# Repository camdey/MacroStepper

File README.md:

# MacroStepper v3.0
Author: Cam Dey

Created: 2018-12-18

v2.0: 2020-01-01

v3.0: 2023-10-11 // refactor, introduces breaking changes

The MacroStepper is a fully automated macrophotography rig designed to enable a camera to take photos at precisely incremented steps. The macroStack can work with or without an automated shutter and also in manual mode if the user prefers to control the stepping themselves.

# Schematic

# Interface
**Home Screen**
 - House icon: _run homing sequence for the rail, finds min and max positions of the rail_
 - X icon: _clears the settings from the auto mode_
 
**Manual Screen**
 - Step Dist: _press to set distance per movement of the motor_
	 - _value is the distance per movement covered by the rail in millimetres_
 - Step Nr: _number of movements taken in manual mode_
 - Rail Pos: _current position of the camera on the rail_
 - Aperture icon: _press to enable/disable automated shutter_
 - X icon: _press to clear step count_
 - Arrows: _for increment/decrementing the Step Size if enabled or moving the rail forward/back otherwise_

**Auto Screen**
 - Step Dist: _press to set distance per movement of the motor_
	 - _value is the distance per movement covered by the rail in millimetres_
 - Est. Time: _estimated time remaining in autoStack procedure. Takes into account shutter delay and the recycle time of the flash unit_
 - Progress: _number of movements completed out of total number of movements in procedure_
 - Aperture icon: _press to enable/disable automated shutter_
 - Cog icon: _opens the config menu for the auto mode_
 - Play symbol: _used to increment Step Size if enabled, otherwise used for starting the autoStack procedure_
 - Pause symbol: _used to decrement Step Size if enabled, otherwise used for pausing the autoStack procedure_

**Config Screen**

 - START: _press to set the start position for the autoStack procedure. Will automatically change to current position when enabled, use joystick or arrows to move rail into correct position_
 - END: _press to set the end position for the autoStack procedure. Will automatically change to current position when enabled, use joystick or arrows to move rail into correct position_
 - RUN: _will move the camera rail to the START position, slowly increment through the autoStack range until it reaches the END, and then move back to the START position_
 - Clock symbol: _press to change the shutter delay between taking photos after each movement of the stepper motor_
 - Arrows: _used to increment/decrement shutter delay or move the position of the rail_

# Functionality
**Flash/Shutter Control**
The camera shutter is controlled by the Arduino via cable where a HIGH signal is sent to a transistor to short the Shutter and Focus pins of the Sony A6000 to ground. The duration of this signal is determined by an output signal from a PC sync cable. This cable is connected to the output of a Godox X1T-S transmitter. This transmitter sends a LOW signal for several milliseconds when the flash is ready to trigger. When the low signal is received by the Arduino, the shutter line goes LOW and the Shutter and Focus pins are returned to nominal state.

**Distance settings**
The step distance setting refers to the distance travelled by the rail per movement. A movement is the sequence of steps required by the stepper motor to travel the set distance. The default distance per step in my case was 25μm, calculated by the following: screw pitch / steps per revolution / gear reduction. My rail had a 1mm pitch and 1:2 gear reduction, while the motor takes 200 steps per revolution.

If the step size is set to 100μm, this equates to four steps at 25μm each. The sequence of these four steps is termed a movement in this project.

**AutoStack Procedure**
The autoStack procedure will increment a range by a given number of movements, determined by the step distance and the start and end positions determined by the user. With a 100μm step distance and 180 steps required to go from the start position to the end position, 45 (180/4) movements are required and thus 45 photos will be taken. The procedure can be paused or reset at any stage and after completion the procedure can be restarted. Both step distance and the end position can be changed during the procedure once paused.

# Macrophotography

## What is focus stacking?

Focus stacking is a method popular within the field of macrophotography where multiple photos of the same subject are taken at different focus depths and then merged together with software. This enables a macro lens with a shallow depth of field to produce an image of a subject that is fully in focus, even if the subject is physically longer than the depth of field of the lens.

## What do you need for Macrophotography?

While you can create a focus stack just with handheld photos taken at different distances from the subject, typically a **macro rail** is used to help with this process. A macro rail allows you to move a camera attached to a platform by very specific distances along a fixed rail or slide. By turning a handle or knob of the macro rail, the camera can be incremented along the rail by distances as small as 25μm or as large as the rail is long.

**Macro Rail**
For this project, you will need a macro rail that can be attached to a stepper motor. Many commercially available macro rails can be retrofitted with a pinion gear to accept a belt, which is in turn attached to a pinion gear on a stepper motor. Other macro rails are designed to interface directly with a stepper motor, especially those designed to be used for CNC machines or 3D printing.

**Stepper Motor**
A stepper motor is required to move the macro rail automatically. You can do this manually, and many do, but after awhile you get sick of the repetitive process of "move camera rail, take photo, move camera rail, take photo".

There are many types of stepper motors available but for this project I would recommend one in the NEMA 17 form factor with either 200 (1.8°) or 400 (0.9°) steps per revolution and between 1A and 2A current rating. The current rating is important for the load the stepper motor can move and hold but it is not the only determiner of this. A motor with a holding torque of at least 3kg-cm should be adequate.

The voltage of the motor is less important as you can supply more voltage than the rated voltage of the motor. More supply voltage typically equals a faster motor.

**Camera and Lens**
Any DSLR or mirrorless camera will be suitable. A macro lens of your choosing is also sufficient.

**Lighting**
I would recommend buying a flash for your camera, preferably wireless. Macrophotography often deals with very low amounts of light and high apertures so a flash is particularly useful. This project is designed to work with the shutter of a Sony multi-terminal port for triggering the shutter and a PC sync cable for detecting the output signal of the flash being triggered but either of these can be changed to the communication methods required for your camera and flash.

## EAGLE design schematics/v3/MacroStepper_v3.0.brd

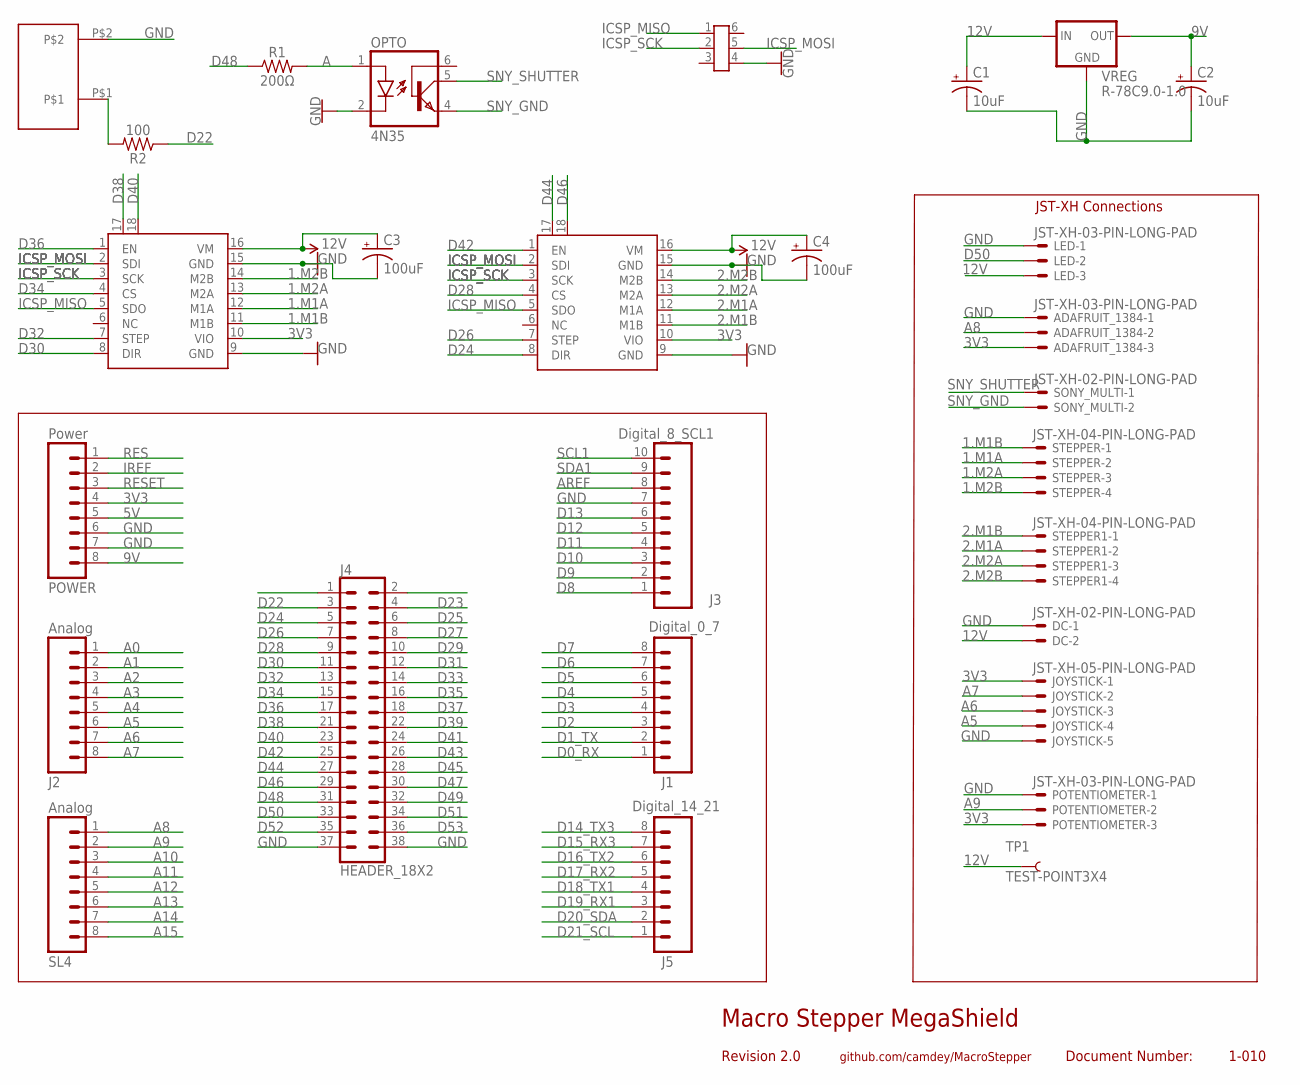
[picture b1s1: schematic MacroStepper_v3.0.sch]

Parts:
ADAFRUIT_1384: JST-XH-03-PIN-LONG-PAD; JST-XH-03-PACKAGE-LONG-PAD
C1, C2: 10uF; CPOL-RADIAL-2.5MM-5MM
C3, C4: 100uF; CPOL-RADIAL-2.5MM-6.5MM
DC: JST-XH-02-PIN-LONG-PAD; JST-XH-02-PACKAGE-LONG-PAD
ICSP: MEGA_ICSP
J1: Digital_0_7; 1X08
J2: Analog; 1X08
J3: Digital_8_SCL1; 1X10
J4: HEADER_18X2; 2X18
J5: Digital_14_21; 1X08
JOYSTICK: JST-XH-05-PIN-LONG-PAD; JST-XH-05-PACKAGE-LONG-PAD
LED: JST-XH-03-PIN-LONG-PAD; JST-XH-03-PACKAGE-LONG-PAD
OPTO: 4N35; DIL06
PIEZO: PS1240P02BT
POTENTIOMETER: JST-XH-03-PIN-LONG-PAD; JST-XH-03-PACKAGE-LONG-PAD
POWER: Power; 1X08
R1: 200Ω; AXIAL-0.3
R2: 100; AXIAL-0.3
SL4: Analog; 1X08
SONY_MULTI: JST-XH-02-PIN-LONG-PAD; JST-XH-02-PACKAGE-LONG-PAD
STEPPER, STEPPER1: JST-XH-04-PIN-LONG-PAD; JST-XH-04-PACKAGE-LONG-PAD
TMC5160_1, TMC5160_2: TMC2130; DIL16
TP1: TEST-POINT3X4; PAD.03X.04
VREG: R-78C9.0-1.0; SIP3

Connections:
1.M1A: STEPPER.2, TMC5160_1.12 (M1A)
1.M1B: STEPPER.1, TMC5160_1.11 (M1B)
1.M2A: STEPPER.3, TMC5160_1.13 (M2A)
1.M2B: STEPPER.4, TMC5160_1.14 (M2B)
2.M1A: STEPPER1.2, TMC5160_2.12 (M1A)
2.M1B: STEPPER1.1, TMC5160_2.11 (M1B)
2.M2A: STEPPER1.3, TMC5160_2.13 (M2A)
2.M2B: STEPPER1.4, TMC5160_2.14 (M2B)
3V3: ADAFRUIT_1384.3, JOYSTICK.1, POTENTIOMETER.3, POWER.4, TMC5160_1.10 (VIO), TMC5160_2.10 (VIO)
5V: POWER.5
9V: C2.1 (+), POWER.8, VREG.3 (OUT)
12V: C1.1 (+), C3.1 (+), C4.1 (+), DC.2, LED.3, TMC5160_1.16 (VM), TMC5160_2.16 (VM), TP1.P$1, VREG.1 (IN)
A: OPTO.1 (A), R1.P$2 (2)
A0: J2.1
A1: J2.2
A2: J2.3
A3: J2.4
A4: J2.5
A5: J2.6, JOYSTICK.4
A6: J2.7, JOYSTICK.3
A7: J2.8, JOYSTICK.2
A8: ADAFRUIT_1384.2, SL4.1
A9: POTENTIOMETER.2, SL4.2
A10: SL4.3
A11: SL4.4
A12: SL4.5
A13: SL4.6
A14: SL4.7
A15: SL4.8
AREF: J3.8
D0_RX: J1.1
D1_TX: J1.2
D2: J1.3
D3: J1.4
D4: J1.5
D5: J1.6
D6: J1.7
D7: J1.8
D8: J3.1
D9: J3.2
D10: J3.3
D11: J3.4
D12: J3.5
D13: J3.6
D14_TX3: J5.8
D15_RX3: J5.7
D16_TX2: J5.6
D17_RX2: J5.5
D18_TX1: J5.4
D19_RX1: J5.3
D20_SDA: J5.2
D21_SCL: J5.1
D22: J4.3 (D22), R2.P$1 (1)
D23: J4.4 (D23)
D24: J4.5 (D24), TMC5160_2.8 (DIR)
D25: J4.6 (D25)
D26: J4.7 (D26), TMC5160_2.7 (STEP)
D27: J4.8 (D27)
D28: J4.9 (D28), TMC5160_2.4 (CS)
D29: J4.10 (D29)
D30: J4.11 (D30), TMC5160_1.8 (DIR)
D31: J4.12 (D31)
D32: J4.13 (D32), TMC5160_1.7 (STEP)
D33: J4.14 (D33)
D34: J4.15 (D34), TMC5160_1.4 (CS)
D35: J4.16 (D35)
D36: J4.17 (D36), TMC5160_1.1 (EN)
D37: J4.18 (D37)
D38: J4.21 (D38), TMC5160_1.17 (DIAG0)
D39: J4.22 (D39)
D40: J4.23 (D40), TMC5160_1.18 (DIAG1)
D41: J4.24 (D41)
D42: J4.25 (D42), TMC5160_2.1 (EN)
D43: J4.26 (D43)
D44: J4.27 (D44), TMC5160_2.17 (DIAG0)
D45: J4.28 (D45)
D46: J4.29 (D46), TMC5160_2.18 (DIAG1)
D47: J4.30 (D47)
D48: J4.31 (D48), R1.P$1 (1)
D49: J4.32 (D49)
D50: J4.33 (D50), LED.2
D51: J4.34 (D51)
D52: J4.35 (D52)
D53: J4.36 (D53)
GND: ADAFRUIT_1384.1, C1.2 (-), C2.2 (-), C3.2 (-), C4.2 (-), DC.1, ICSP.4 (GND), J3.7, J4.37 (GND), J4.38 (GND), JOYSTICK.5, LED.1, OPTO.2 (C), PIEZO.P$2, POTENTIOMETER.1, POWER.6, POWER.7, TMC5160_1.9 (GND), TMC5160_1.15 (GND), TMC5160_2.9 (GND), TMC5160_2.15 (GND), VREG.2 (GND)
ICSP_MISO: ICSP.1 (MISO), TMC5160_1.5 (SDO), TMC5160_2.5 (SDO)
ICSP_MOSI: ICSP.5 (MOSI), TMC5160_1.2 (SDI), TMC5160_2.2 (SDI)
ICSP_SCK: ICSP.2 (SCK), TMC5160_1.3 (SCK), TMC5160_2.3 (SCK)
IREF: POWER.2
unnamed: PIEZO.P$1, R2.P$2 (2)
RES: POWER.1
RESET: POWER.3
SCL1: J3.10
SDA1: J3.9
SNY_GND: OPTO.4 (EMI), SONY_MULTI.2
SNY_SHUTTER: OPTO.5 (COL), SONY_MULTI.1

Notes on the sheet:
JST-XH Connections
Macro Stepper MegaShield
Revision 2.0
github.com/camdey/MacroStepper
Document Number:
1-010

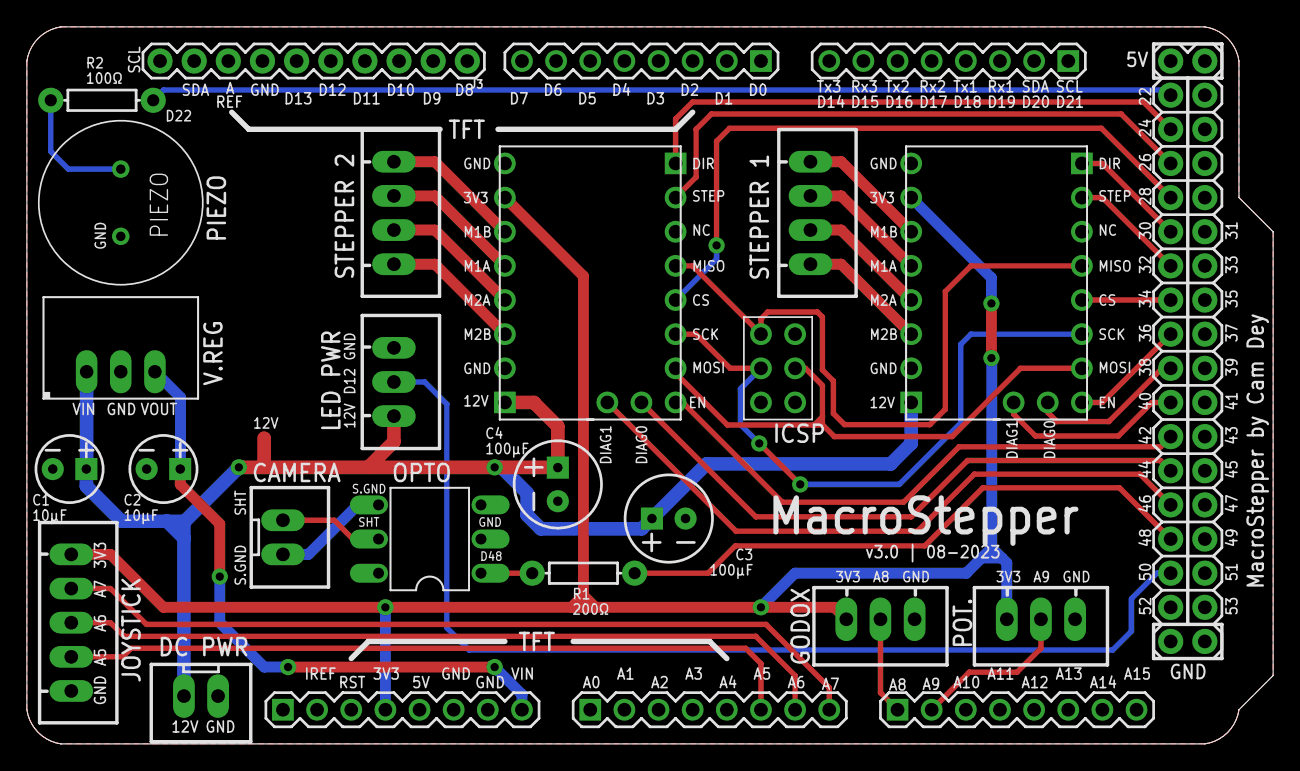
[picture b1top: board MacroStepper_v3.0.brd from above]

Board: 2 copper layers, 92.7 x 53.3 mm, 29 parts (1 on the bottom side), 39 nets.

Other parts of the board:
U$1: ARTEMIS_LOGO_LARGE

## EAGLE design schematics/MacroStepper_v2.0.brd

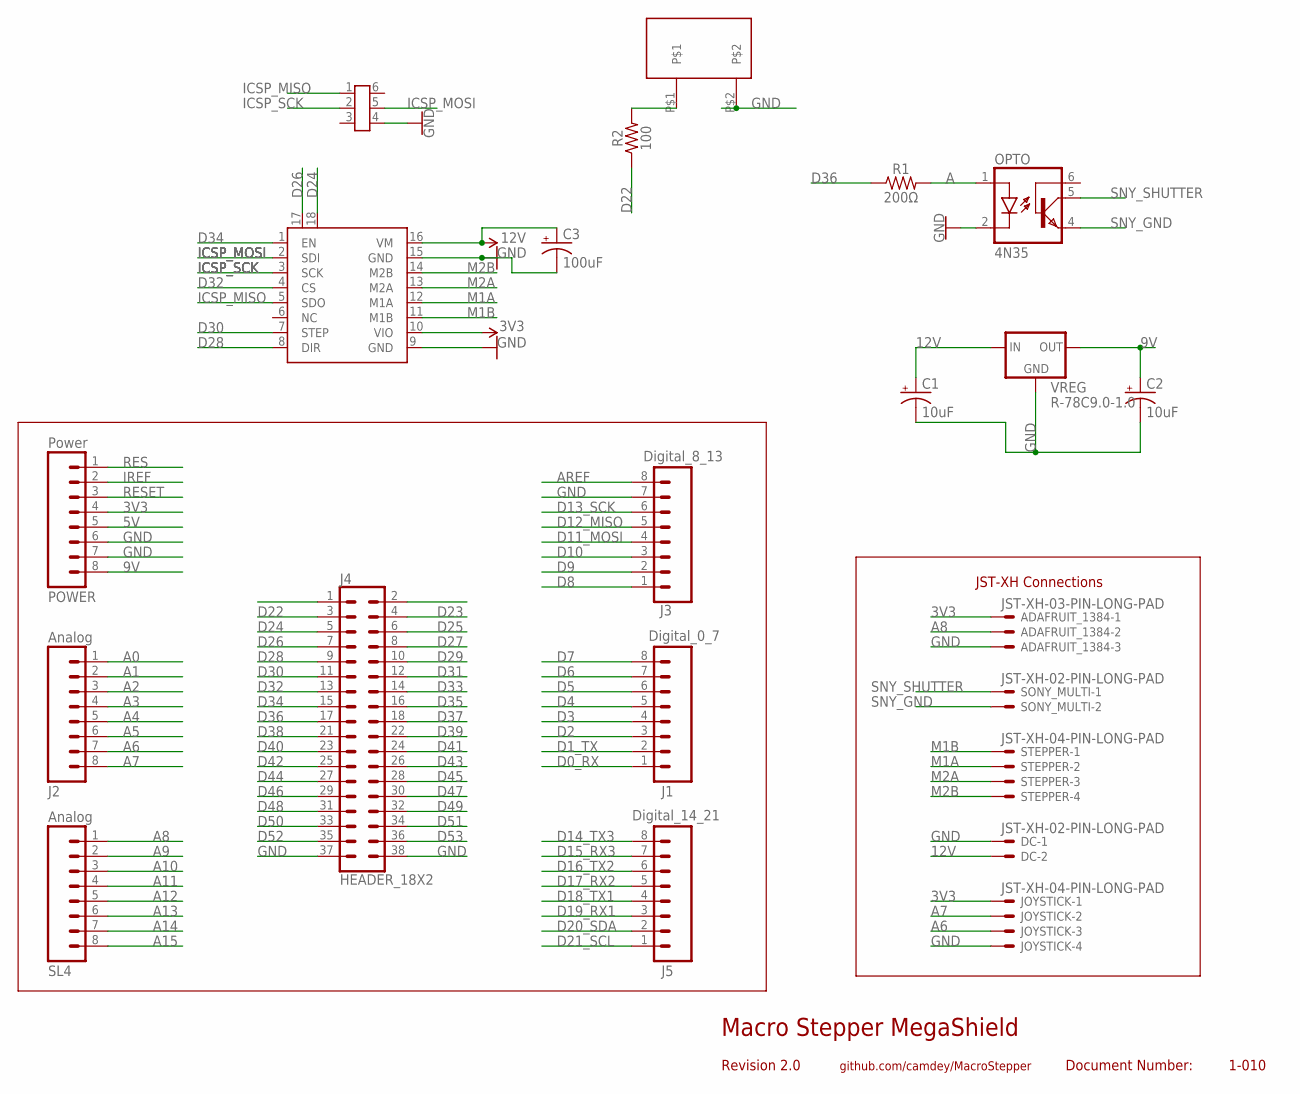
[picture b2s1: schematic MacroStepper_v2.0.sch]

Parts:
ADAFRUIT_1384: JST-XH-03-PIN-LONG-PAD; JST-XH-03-PACKAGE-LONG-PAD
C1, C2: 10uF; CPOL-RADIAL-2.5MM-5MM
C3: 100uF; CPOL-RADIAL-2.5MM-6.5MM
DC: JST-XH-02-PIN-LONG-PAD; JST-XH-02-PACKAGE-LONG-PAD
ICSP: MEGA_ICSP
J1: Digital_0_7; 1X08
J2: Analog; 1X08
J3: Digital_8_13; 1X08
J4: HEADER_18X2; 2X18
J5: Digital_14_21; 1X08
JOYSTICK: JST-XH-04-PIN-LONG-PAD; JST-XH-04-PACKAGE-LONG-PAD
OPTO: 4N35; DIL06
PIEZO: PS1240P02BT
POWER: Power; 1X08
R1: 200Ω; AXIAL-0.3
R2: 100; AXIAL-0.3
SL4: Analog; 1X08
SONY_MULTI: JST-XH-02-PIN-LONG-PAD; JST-XH-02-PACKAGE-LONG-PAD
STEPPER: JST-XH-04-PIN-LONG-PAD; JST-XH-04-PACKAGE-LONG-PAD
TMC2130: TMC2130; DIL16
VREG: R-78C9.0-1.0; SIP3

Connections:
3V3: ADAFRUIT_1384.1, JOYSTICK.1, POWER.4, TMC2130.10 (VIO)
5V: POWER.5
9V: C2.1 (+), POWER.8, VREG.3 (OUT)
12V: C1.1 (+), C3.1 (+), DC.2, TMC2130.16 (VM), VREG.1 (IN)
A: OPTO.1 (A), R1.P$2 (2)
A0: J2.1
A1: J2.2
A2: J2.3
A3: J2.4
A4: J2.5
A5: J2.6
A6: J2.7, JOYSTICK.3
A7: J2.8, JOYSTICK.2
A8: ADAFRUIT_1384.2, SL4.1
A9: SL4.2
A10: SL4.3
A11: SL4.4
A12: SL4.5
A13: SL4.6
A14: SL4.7
A15: SL4.8
AREF: J3.8
D0_RX: J1.1
D1_TX: J1.2
D2: J1.3
D3: J1.4
D4: J1.5
D5: J1.6
D6: J1.7
D7: J1.8
D8: J3.1
D9: J3.2
D10: J3.3
D11_MOSI: J3.4
D12_MISO: J3.5
D13_SCK: J3.6
D14_TX3: J5.8
D15_RX3: J5.7
D16_TX2: J5.6
D17_RX2: J5.5
D18_TX1: J5.4
D19_RX1: J5.3
D20_SDA: J5.2
D21_SCL: J5.1
D22: J4.3 (D22), R2.P$1 (1)
D23: J4.4 (D23)
D24: J4.5 (D24), TMC2130.18 (DIAG1)
D25: J4.6 (D25)
D26: J4.7 (D26), TMC2130.17 (DIAG0)
D27: J4.8 (D27)
D28: J4.9 (D28), TMC2130.8 (DIR)
D29: J4.10 (D29)
D30: J4.11 (D30), TMC2130.7 (STEP)
D31: J4.12 (D31)
D32: J4.13 (D32), TMC2130.4 (CS)
D33: J4.14 (D33)
D34: J4.15 (D34), TMC2130.1 (EN)
D35: J4.16 (D35)
D36: J4.17 (D36), R1.P$1 (1)
D37: J4.18 (D37)
D38: J4.21 (D38)
D39: J4.22 (D39)
D40: J4.23 (D40)
D41: J4.24 (D41)
D42: J4.25 (D42)
D43: J4.26 (D43)
D44: J4.27 (D44)
D45: J4.28 (D45)
D46: J4.29 (D46)
D47: J4.30 (D47)
D48: J4.31 (D48)
D49: J4.32 (D49)
D50: J4.33 (D50)
D51: J4.34 (D51)
D52: J4.35 (D52)
D53: J4.36 (D53)
GND: ADAFRUIT_1384.3, C1.2 (-), C2.2 (-), C3.2 (-), DC.1, ICSP.4 (GND), J3.7, J4.37 (GND), J4.38 (GND), JOYSTICK.4, OPTO.2 (C), PIEZO.P$2, POWER.6, POWER.7, TMC2130.9 (GND), TMC2130.15 (GND), VREG.2 (GND)
ICSP_MISO: ICSP.1 (MISO), TMC2130.5 (SDO)
ICSP_MOSI: ICSP.5 (MOSI), TMC2130.2 (SDI)
ICSP_SCK: ICSP.2 (SCK), TMC2130.3 (SCK)
IREF: POWER.2
M1A: STEPPER.2, TMC2130.12 (M1A)
M1B: STEPPER.1, TMC2130.11 (M1B)
M2A: STEPPER.3, TMC2130.13 (M2A)
M2B: STEPPER.4, TMC2130.14 (M2B)
unnamed: PIEZO.P$1, R2.P$2 (2)
RES: POWER.1
RESET: POWER.3
SNY_GND: OPTO.4 (EMI), SONY_MULTI.2
SNY_SHUTTER: OPTO.5 (COL), SONY_MULTI.1

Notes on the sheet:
JST-XH Connections
Macro Stepper MegaShield
Revision 2.0
github.com/camdey/MacroStepper
Document Number:
1-010

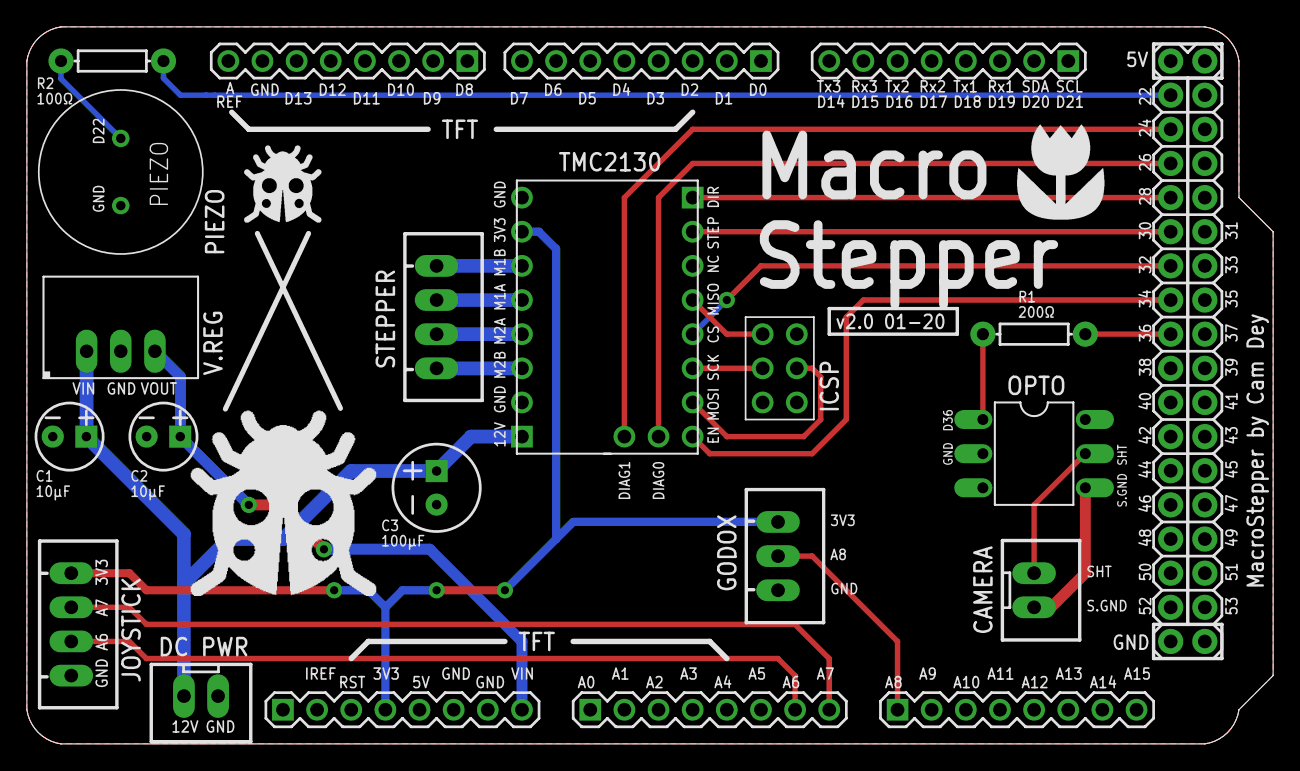
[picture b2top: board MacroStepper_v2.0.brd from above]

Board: 2 copper layers, 92.7 x 53.3 mm, 22 parts (0 on the bottom side), 26 nets.

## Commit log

2018-12-18 first commit of tft test
2018-12-19 start screen layout + manual_screen work
2018-12-21 changes to manual step screen
2018-12-22 finish screen drafts, add first touch nav
2018-12-22 Create README.txt file
2018-12-24 more touch functionality
2018-12-25 autoconfig touches
2019-01-17 intergrates stepper motor controls from earlier arduino file
2019-01-19 fixes single step functionality, adds adjustable step distance
2019-01-20 implements start/end and run functionality
2019-01-20 more changes to start/end/run
2019-01-21 starts implementation of macro stepping, adds shutter support, updates rail pos. in manual mode, changes menu design
2019-01-22 change autoscreen menu, fix bugs, implement pause, add progress counter
2019-01-23 changes variable names for consistency in terminology
2019-01-23 adds manual functionality, reset, shutter trigger func, play/pause, bug fixes
2019-01-24 bug fixes, est. time functionality, manaul shutter, etc
2019-01-26 converted all interval/delay variables to unsigned long to fix bug
2019-01-27 bug fixes: reverse step issue, number updates. Added symbols etc
2019-01-28 adds logo, back button symbol, changes limit positions to after push-off
2019-01-29 finished adding symbols, changed button colours
2019-02-12 adds functionality for flash recycle time
2019-02-17 adds schematic
2019-02-17 update readme with schematic and pinouts
2019-02-17 cleans up some stuff
2019-02-25 refactors stepping functions, autostack, fixes manual step bug, sleeping changed to en able pin
2019-03-18 creates branch, some small preparatory changes
2019-03-20 fixed font files, moved to project folder
2019-06-22 major updates: support for tmc2130, stall detection, remove limit switches, use light sensor for flash recycle
2019-06-27 compartmentalise symbols into separate files
2019-06-27 small fixes
2019-06-28 moving code blocks to separate files
2019-06-28 completes splitting out functions into separate files
2019-06-29 minor bug fixes
2019-06-29 more bug fixes, new function for updating values on screen
2019-06-30 small fixes to est time
2019-06-30 Create .editorconfig file
    fixes indentation display on github
2019-06-30 function for handling unexpected light sensor readings
2019-07-02 adds more flash testing functionality
2019-07-02 completes Flash screen and functionality
2019-07-04 minor debugging fixes
2019-07-09 small bug fixes
2019-07-15 functionality for preventing jerk when using joystick
2019-07-19 implements screen rotation to use controller with joystick on either left right side
2019-07-19 fixed bug with inverted joystick reading exceeding threshold
2019-07-19 adding rotate_icon
2019-07-26 implemented pause stack on flash failure, fixed movementsRequired calc.
2019-08-01 Update README.md
    Adding note about lack of documentation for recent hardware changes
2019-08-01 Update README.md
    New line
2019-09-05 bug fixes
2019-09-05 update schematic
2019-09-05 add new schematic to readme
2020-01-18 add due support, mcufriend master, manual CS control
2020-03-13 test Grand Central + new PCB
2020-03-15 small adjustments for arduino due
2020-03-22 joystic, homing, tft working on Arduino Due
2020-03-22 split joystick into new cpp, fix issue with missing steps in autoStack start, add overshoot function for backlash
2020-03-22 add eagle files and pcb images
2020-03-22 Update README.md
    add new PCB image, update pinouts
2020-03-22 use images from master branch
2020-03-23 first implementation of button library
2020-03-24 replace arrows with bitmaps, add tft-main
2020-03-25 implement button draw and check routine
2020-03-26 start flash screen implementation
2020-03-29 drafted home, manual, flash pages
2020-03-31 updated arrow icons, tested home, manual, flash pages
2020-04-03 small bug fixes, improvements
2020-04-04 added Auto screen
2020-04-05 add autoConfig screen
2020-04-10 complete AutoConfig draft, clean up and deprecate
2020-04-10 minor bug fixes and cleaning up
2020-04-11 refactor for 3.5 inch display
2020-04-12 refactor flash and auto screens for 3.5 inch
2020-04-12 refactor autoconfig screen for 3.5 inch
2020-04-13 small bug fixes, change arrays to array of pointers
2020-04-13 small tweaks and fixes
2020-06-07 replace joystick functions with tmc5160 compatible functions
2020-07-13 add new homing routine, deprecate stepper.()
2020-07-14 test homing
2020-07-15 implement homing for tmc5160
2020-07-15 implement homing and joystick control for tmc5160
2020-07-16 fix joystick issues, tidy up code
2020-07-17 refactor global variable usage
2020-07-17 refactor variables into get/set methods, start AutoStack refactor for tmc5160
2020-07-18 bug fixes, cleaning up
2020-07-19 more refactoring, fix dryRun procedure, reduce global variables, add tone library
2020-07-19 ignore .vscode folder
2020-07-19 remove and ignore .vscode/ folder from branch
2020-07-20 more refactoring, bug fixes, code clean up
2020-07-21 fix joystick overshoot and position update synchronisation
2020-07-25 refactor flash functions
2020-07-26 fix play/pause bug, add delay after flash
2020-08-15 minor clean up changes
2020-08-15 update UI to use new gfxButton refactor
2020-08-15 bug fixes for btn refactor
2020-08-16 add global buttons
2020-08-16 implement hidden buttons for play/pause and arrows
2020-08-16 add global button files
2020-08-29 add target screen
2020-10-19 improve flash function, add bulb disable, small bug fixes
2020-10-21 improve flash procedure function
2020-10-24 add stack status messaging
2021-06-20 move ui files to subdir
2021-06-20 add orbis functionality
2021-06-25 add video360 functionality
2021-06-25 video360 bugs
2021-06-25 add photo360 page, rename video/photo objects
2021-06-26 implement photo360 routine
2021-06-26 photo360 fixes
2021-06-27 add config page for photo360
2021-06-27 finish orbis implementation, small fixes
2021-06-27 fix button alignment
2022-01-04 add functionality for 360 photos and videos
2023-07-25 small fixes and improvements
2023-07-25 update tmc driver registers to reflect new naming
2023-07-28 decrease min. shutter delay and convert it to milliseconds
2023-08-26 initial refactoring to v3 PCB and dual stepper drivers
2023-08-26 fix indents
2023-08-27 extend tmc5160 class, refactor functions to accept instances of stepper
2023-08-27 more refactoring
2023-08-27 contuinue refactor, rename driverconfig to stepperconfig
2023-08-27 fix external stepper var
2023-08-27 fix func not setting vmax, cs enable logic
2023-08-28 add autostack class, refactor indents to 4 spaces
2023-08-29 refactor of AutoStack methods, add class
2023-08-29 more autostack refactoring
2023-08-30 update auto ui page and others with autostack refactor
2023-08-31 create flash class for flash and shutter methods
2023-09-01 continue adding class for shutter/flash controls
2023-09-02 continue refactoring, camera class finished
2023-09-03 add photo360 class, fix remaining errors
2023-09-03 add class for user_interface, joystick
2023-09-03 fix bugs stemming from ui class refactor
2023-09-05 minor refactoring for adding control of 2nd stepper
2023-09-09 fix joystick ctor, slaveSelected mapping
2023-09-09 fix bug in configstealthchop that meant it was never run
2023-09-10 add led class, fix bugs in autostack
2023-10-08 fix photo360, implement video360, fix AutoStack bugs
2023-10-11 update readme, add new pcb
2023-10-11 add back schematics, update readme img url
2023-10-14 add suppor fort rgb bitmap buttons
2023-10-16 add side menu, new icons
2023-10-21 add new icons, replace old icons, ui tweaks
2023-10-22 add more rgb icons
2023-10-22 add more icons
2023-10-30 move large icons to sd card
2023-10-31 add new fonts, ui changes
2023-11-04 add piezo class, minor fixes and upgrades
2024-01-21 various improvements

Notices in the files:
parts and their libraries:
SparkFun-Capacitors: Licensing: Creative Commons ShareAlike 4.0 International - https://creativecommons.org/licenses/by-sa/4.0
r-78xx_10: (c) 2015 Samuel Lourenço
